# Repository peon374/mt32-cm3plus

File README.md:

# mt32-cm3plus
This is a CM3+ version of the MT32Pi hardware. All layout is done in Kicad and I will create release files with everything needed to get a run of boards done and half assembled with jlcpcb.

This project is a hardware implementation designed to work with [MT32-Pi](https://github.com/dwhinham/mt32-pi)

_THIS IS A WORK IN PROGRESS AND ISN'T COMPLETE_

You should not build this till there are is a working release. The convention I will be using is to call something a release candidate (RC) till I know everything I have added works and I have reasonable documentation. If you do not see reasonable documentation, either contribute doco, ideas or bugs you can see in what I have done. The plan is to have everything that can be populated out of JLCPCB basic parts on the underside so that a lot of the fiddly bits are already done. The SODIMM connector for the CM3+ is not simple if you don't have a good iron and good flux. Both can be found on Aliexpress with a bit of research but flux is more of a gamble.

I plan to continue improving the device, so if you have any ideas put them in.

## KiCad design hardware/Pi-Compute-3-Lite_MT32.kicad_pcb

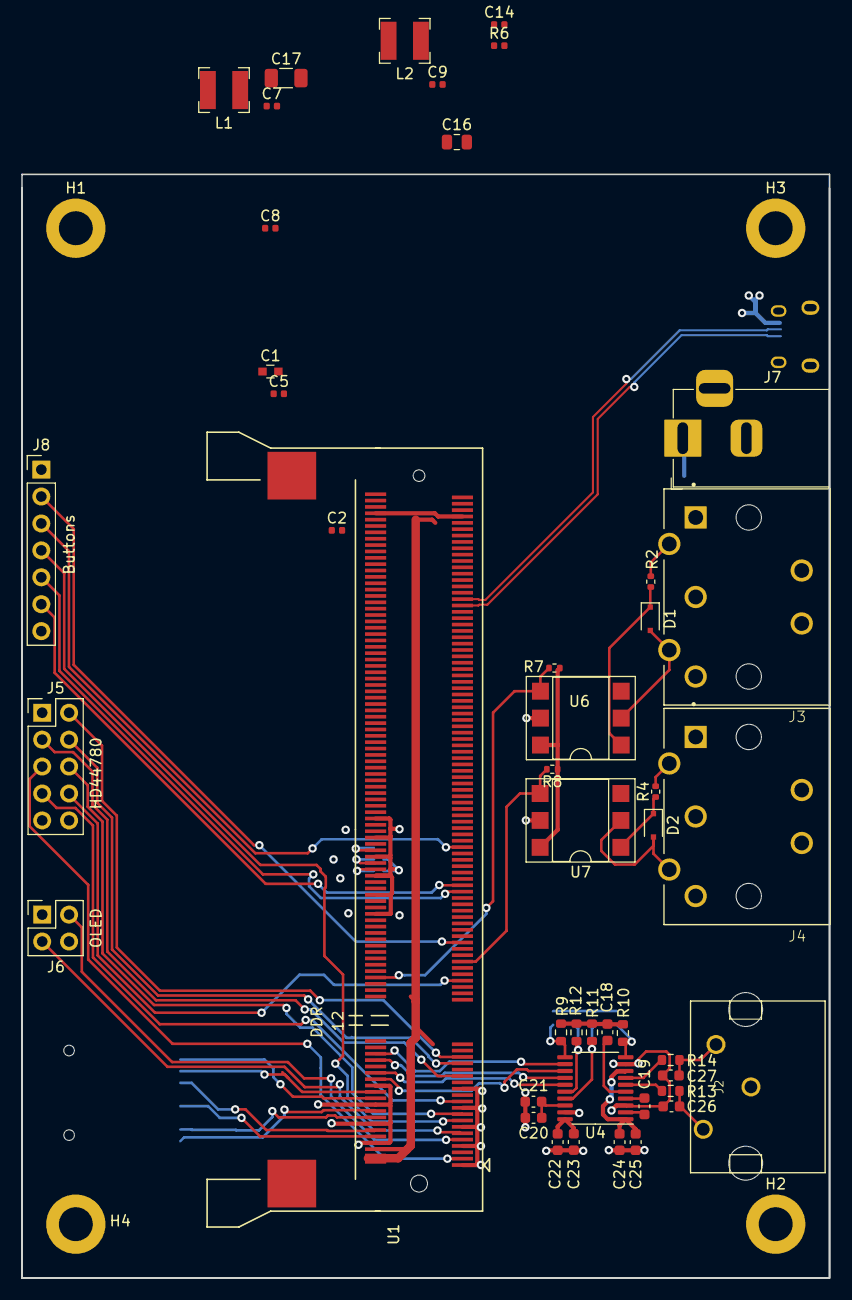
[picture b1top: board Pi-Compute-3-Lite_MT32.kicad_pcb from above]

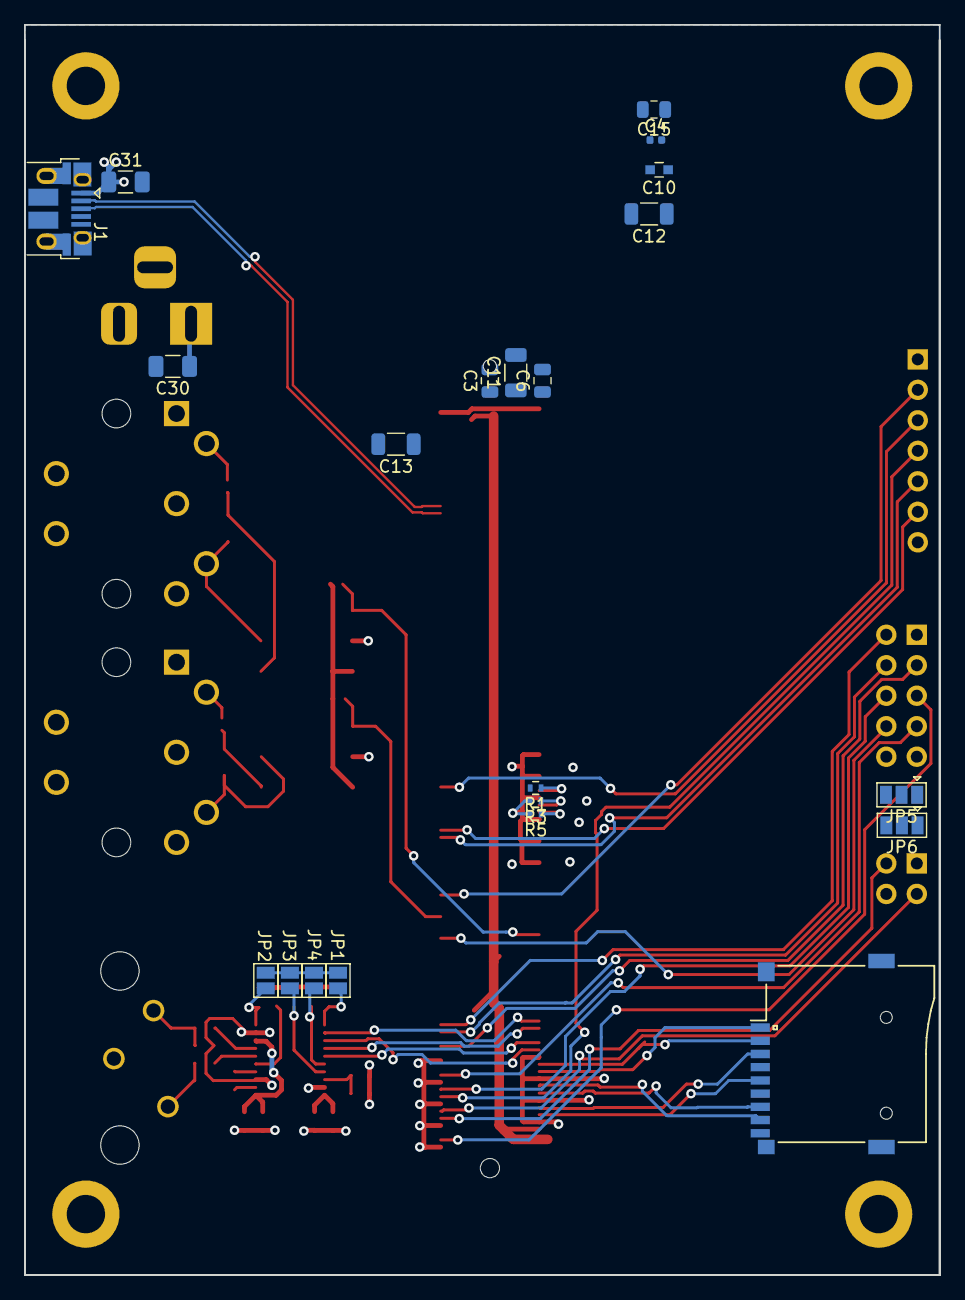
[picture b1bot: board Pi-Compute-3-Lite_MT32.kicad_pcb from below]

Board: 2 copper layers, 76.2 x 104.1 mm, 70 parts (21 on the bottom side), 60 nets.

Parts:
C1, C10: 4.7uF; C_0603
C2, C7, C9: 100nF; C_0402_1005Metric
C3, C6, C15, C16: 10uF; C_0805_2012Metric
C4, C5, C8: 1uF; C_0402_1005Metric
C11, C12, C13, C17, C30, C31: 47uF; C_1206_3216Metric
C14: 4.7uF; C_0402_1005Metric
C18, C19: 2.2uF; C_0603_1608Metric
C20, C22, C24: 10uF; C_0603_1608Metric
C21, C23, C25: 100nF; C_0603_1608Metric
C26, C27: 2.2nF; C_0603_1608Metric
D1, D2: 1N4148; D_SOD-323F
H1, H2, H3, H4: M3; MountingHole_3.2mm_M3_DIN965_Pad
J1: USB_B_Micro; USB_Micro-B_Amphenol_10103594-0001LF_Horizontal
J2: Conn_Coaxial_x2; DUALRCA
J3, J4: MIDI-IN; SWITCHCRAFT_57PC5FS
J5: HD44780; PinHeader_2x05_P2.54mm_Vertical
J6: OLED; PinHeader_2x02_P2.54mm_Vertical
J7: Barrel_Jack; BarrelJack_Horizontal
J8: Buttons; PinHeader_1x07_P2.54mm_Vertical
JP1, JP2, JP3, JP4: Jumper_2_Open; SolderJumper-2_P1.3mm_Open_Pad1.0x1.5mm
JP5, JP6: LCD_PWR; SolderJumper-3_P1.3mm_Open_Pad1.0x1.5mm
L1, L2: 4.7uH; L_Bourns-SRN4018
R1, R3, R5: 100k; R_0402
R2, R4: 220R; R_0402_1005Metric
R6: 100k; R_0402_1005Metric
R7, R8: 1K; R_0402_1005Metric
R9, R10, R11, R12: 100k; R_0603_1608Metric
R13, R14: 470; R_0603_1608Metric
U1: DDR2_SODIMM_CM_3_Lite; Socket_SODIMM_DDR2
U4: PCM5102; TSSOP-20_4.4x6.5mm_P0.65mm
U6, U7: H11L1; DIP-6_W7.62mm_SMDSocket_SmallPads
XS1: SD_ebay-uSD-push_push_SMD; Conn_uSDcard

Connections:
3V3: C1.1, C8.1, C10.1, U1.2, U1.4, U1.6, XS1.4
+5V: JP5.3, JP6.3
/Raspberry PI CM3+/ENC_CLK: J8.5, U1.75
/Raspberry PI CM3+/ENC_DAT: J8.6, U1.77
/Raspberry PI CM3+/LCD_D4: J5.5, U1.3
/Raspberry PI CM3+/LCD_D5: J5.6, U1.17
/Raspberry PI CM3+/LCD_D6: J5.7, U1.21
/Raspberry PI CM3+/LCD_D7: J5.8, U1.47
/Raspberry PI CM3+/LCD_EN: J5.2, U1.35
/Raspberry PI CM3+/LCD_RS: J5.4, U1.33
/Raspberry PI CM3+/LCD_RW: J5.3, U1.29
/Raspberry PI CM3+/OLED_SCL: J6.3, U1.11
/Raspberry PI CM3+/OLED_SDA: J6.2, U1.9
/Raspberry PI CM3+/UX_B1: J8.2, U1.59
/Raspberry PI CM3+/UX_B2: J8.3, U1.89
/Raspberry PI CM3+/UX_B3: J8.4, U1.15
CM_1V8: C13.1, C16.1, L2.2, U1.183, U1.184, U1.185, U1.186
CM_3V3: C4.1, C5.1, C12.1, C15.1, J8.1, JP5.1, JP6.1, L1.2, R7.1, R8.1, U1.39, U1.40, U1.41, U1.42, U1.191, U1.192, U1.193, U1.194, U6.6, U7.6
CM_VBAT: C3.1, C6.1, C11.1, C30.1, C31.1, J1.1, J7.1, R6.1, U1.197, U1.198, U1.199, U1.200
CM_VDAC: C2.1, U1.189, U1.190
DAC_BCK: U1.28, U4.13
DAC_DIN: U1.34, U4.14
DAC_LRCK: U1.30, U4.15
DAC_SCK: U1.36, U4.12
GND: C1.2, C2.2, C3.2, C4.2, C5.2, C6.2, C7.2, C8.2, C9.2, C10.2, C11.2, C12.2, C13.2, C14.2, C15.2, C16.2, C17.2, C18.2, C20.2, C21.2, C22.2, C23.2, C24.2, C25.2, C26.2, C27.2, C30.2, C31.2, H1.1, H2.1, H3.1, H4.1, J1.5, J1.6, J2.3, J5.9, J5.10, J6.4, J7.2, J8.7, R3.2, R5.2, R9.2, R10.2, R11.2, R12.2, U1.1, U1.7, U1.8, U1.13, U1.14, U1.19, U1.20, U1.25, U1.26, U1.31, U1.32, U1.37, U1.38, U1.43, U1.44, U1.49, U1.50, U1.55, U1.56, U1.61, U1.62, U1.67, U1.68, U1.73, U1.74, U1.79, U1.80, U1.85, U1.86, U1.91, U1.92, U1.97, U1.98, U1.103, U1.104, U1.109, U1.110, U1.115, U1.116, U1.121, U1.122, U1.127, U1.133, U1.134, U1.139, U1.140, U1.145, U1.146, U1.151, U1.152, U1.157, U1.163, U1.164, U1.169, U1.170, U1.181, U1.182, U1.187, U1.188, U1.195, U1.196, U4.3, U4.9, U4.19, U6.5, U7.5, XS1.6
MIDI-RX1: R7.2, U1.48, U6.4
MIDI-RX2: R8.2, U1.53, U7.4
unnamed: C7.1, R6.2
unnamed: C18.1, U4.5
unnamed: C19.1, U4.4
unnamed: C19.2, U4.2
unnamed: C20.1, C21.1, U4.18
unnamed: C26.1, J2.2, R13.1
unnamed: C27.1, J2.1, R14.1
unnamed: J5.1, JP5.2
unnamed: J6.1, JP6.2
unnamed: D1.1, R2.1, U6.1
unnamed: D1.2, J3.5, U6.2
unnamed: D2.1, R4.1, U7.1
unnamed: D2.2, J4.5, U7.2
unnamed: J3.4, R2.2
unnamed: J4.4, R4.2
unnamed: JP1.2, R9.1, U4.11
unnamed: JP2.2, R10.1, U4.10
unnamed: JP3.2, R11.1, U4.17
unnamed: JP4.2, R12.1, U4.16
unnamed: R1.1, U1.88
unnamed: R3.1, U1.84
unnamed: R5.1, U1.82
unnamed: R13.2, U4.6
unnamed: R14.2, U4.7
SDX_CLK: U1.10, XS1.5
SDX_CMD: U1.12, XS1.3
SDX_D0: U1.16, XS1.7
SDX_D1: U1.18, XS1.8
SDX_D2: U1.22, XS1.1
SDX_D3: U1.24, XS1.2
USB_D+: J1.3, U1.165
USB_D-: J1.2, U1.167
VDD: C22.1, C23.1, C24.1, C25.1, JP1.1, JP2.1, JP3.1, JP4.1, U4.1, U4.8, U4.20

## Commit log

2021-09-17 Added start
2021-09-18 Cleaning up the power section
2021-09-19 Cleanup libs
